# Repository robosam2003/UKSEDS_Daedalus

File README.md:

# UKSEDS Team Daedalus - "In thrust we trust"

The rocket avionics consisted of a Teensy 4.1 for the main microcontoller, a low-g IMU (BNO055), a high-g accelerometer (ADXL377), a pressure sensor (BMP280), a GPS (NEO-6M) and a 433 MHz radio transciever (RFM96W).

The purpose of the rocket was to collect acceleration and gyroscope data such that we could test our IMU based position estimation algorithm (also called dead reckoning).

# Code
The `code` folder contains code for all the sensors and telemetry onboard and for the ground station. The `masterCode` folder contains the final code loaded onto the rocket.

## Sensors and telemetry:
- **BNO055**: Our low-g IMU, containing accelerometers capable of ±16G, as well as very accurate gyroscopes and magnetometers. Big thanks to SunrIde's [Tom Danvers](https://github.com/TomD53) for writing the library we used to interface with the BNO055: [`Arduino-BNO055`](https://github.com/TeamSunride/Arduino-BNO055). 
- **ADXL377**: Our high-g IMU, capable of up to ±200G. This is an analogue sensor and is *very noisy*, so both hardware filters (capacitors) and software filters ([Kalman filters](https://github.com/denyssene/SimpleKalmanFilter)) were used to get accurate data. 
- **BMP280**: A pressure based altimeter used in conjunction with the brilliant [Adafruit library](https://github.com/adafruit/Adafruit_BMP280_Library).
- **NEO-6M**: A cheap but capable GPS module from ublox. In order to get a fast GPS lock, we implemented assisted GPS loading using the ublox AssistNow service. See [`code/NEO6mWithAssistNow`](https://github.com/robosam2003/UKSEDS_Daedalus/tree/main/code/NEO6mWithAssistNow).
- **RFM96W**: A 433MHz SX1272 based tranciever module that was used both onboard and on our ground station. We used the LoRa protocol for greater range. We implemented an interrupt driven method using [`RadioLib`](https://github.com/jgromes/RadioLib).

## Ground station
The ground station used an old arduino nano with the RFM96W to recieve live telemetrics from the rocket. The launch commit button was used to put the rocket into a launch ready state remotely.

It passed this data to Grafana and InfluxDB using the [line protocol](https://docs.influxdata.com/influxdb/cloud/reference/syntax/line-protocol/). Big thanks to SunrIde's [Yomi](https://github.com/abayomi185), [Tom](https://github.com/TomD53) and [Sebastiano](https://github.com/robosam2003/UKSEDS_Daedalus/blob/main/resources/grafanaDashboard.jpg) for building the software to do this [`TeamSunride/GroundStation`](https://github.com/TeamSunride/GroundStation). Our live telemetry Grafana Dashboard is shown below:

### The rocket launch sequence is as follows:
- Ensure ground station is booted and ready.
- **Compile** masterCode/main.cpp and upload to teensy so that the RTC syncs.
- Setup sensors, datalogging and telemety on the ground.
- Full system test with serial output to double check sensor values look reasonable.
- Load avionics into rocket.
- Wait for "Launch commit" from ground station.
- When rocket is loaded on the launch rail, press launch commit button on ground station (wait for confirmation - ground station light should go green).
- Start data acquisition, datalogging and transmitting data.
- Launch!

Loading avionics:

# Circuitry
This rocket used breakout boards to house components. This made testing and verification easier before ordering the final PCB. The PCB was designed in EAGLE using many custom libraries. 

The final schematic:

[`Rocketry_circuit.sch`](https://github.com/robosam2003/UKSEDS_Daedalus/blob/main/circuitry/Rocketry_circuit.sch):

The final pcb board design:

[`Rocketry_circuit.brd`](https://github.com/robosam2003/UKSEDS_Daedalus/blob/main/circuitry/Rocketry_circuit.brd):

The manufactured PCB (from china):   

The assembled pcb with breakouts soldered and mounted:

The avionics recovered after flight:

# Flight data

The launch was a ~success!~... it *went up* anyway. We suspect excess friction on the launch rail caused it to fly off course at about a 45° angle. (See https://www.youtube.com/watch?v=rMJzLpDIJ3U)

The rocket still achieved an apogee of 641m according to the BMP280 altimeter (note that the spike at apogee caused by the pressure from the ejection charge). The GPS lost satellite lock on launch as predicted, but regrained lock after apogee:

The acceleration data followed our expectations from the OpenRocket simulation, with a slightly lower max acceleration of 14.4g. Unfortunately, the BNO055 maxed out at 4G, rather than the desired 16g, despite having configured it to read up to 16g. The ADXL377 data is decent though: (note the spike at ejection charge)

The onboard dead reckoning algorithm also didn't work as expected, due to the BNO055 maxing out earlier than anticipated and due to the initial launch being so oscillatory (which threw off orientation estimation) the data is not an accurate measurement of position. Much has been learned from this launch and will be refined in future rockets. :)

The **telemetry** range was not very good, likely due to bad antennas, and because of UK regulations which limited our transmit power down to 10dbm at a max duty cycle of 10%. :(

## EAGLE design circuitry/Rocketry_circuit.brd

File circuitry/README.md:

This is the folder for circuitry

.brd files contain files relating to pcb placement and copper routing

.sch files contain schematics\n

.pro files contin autorouter data\n

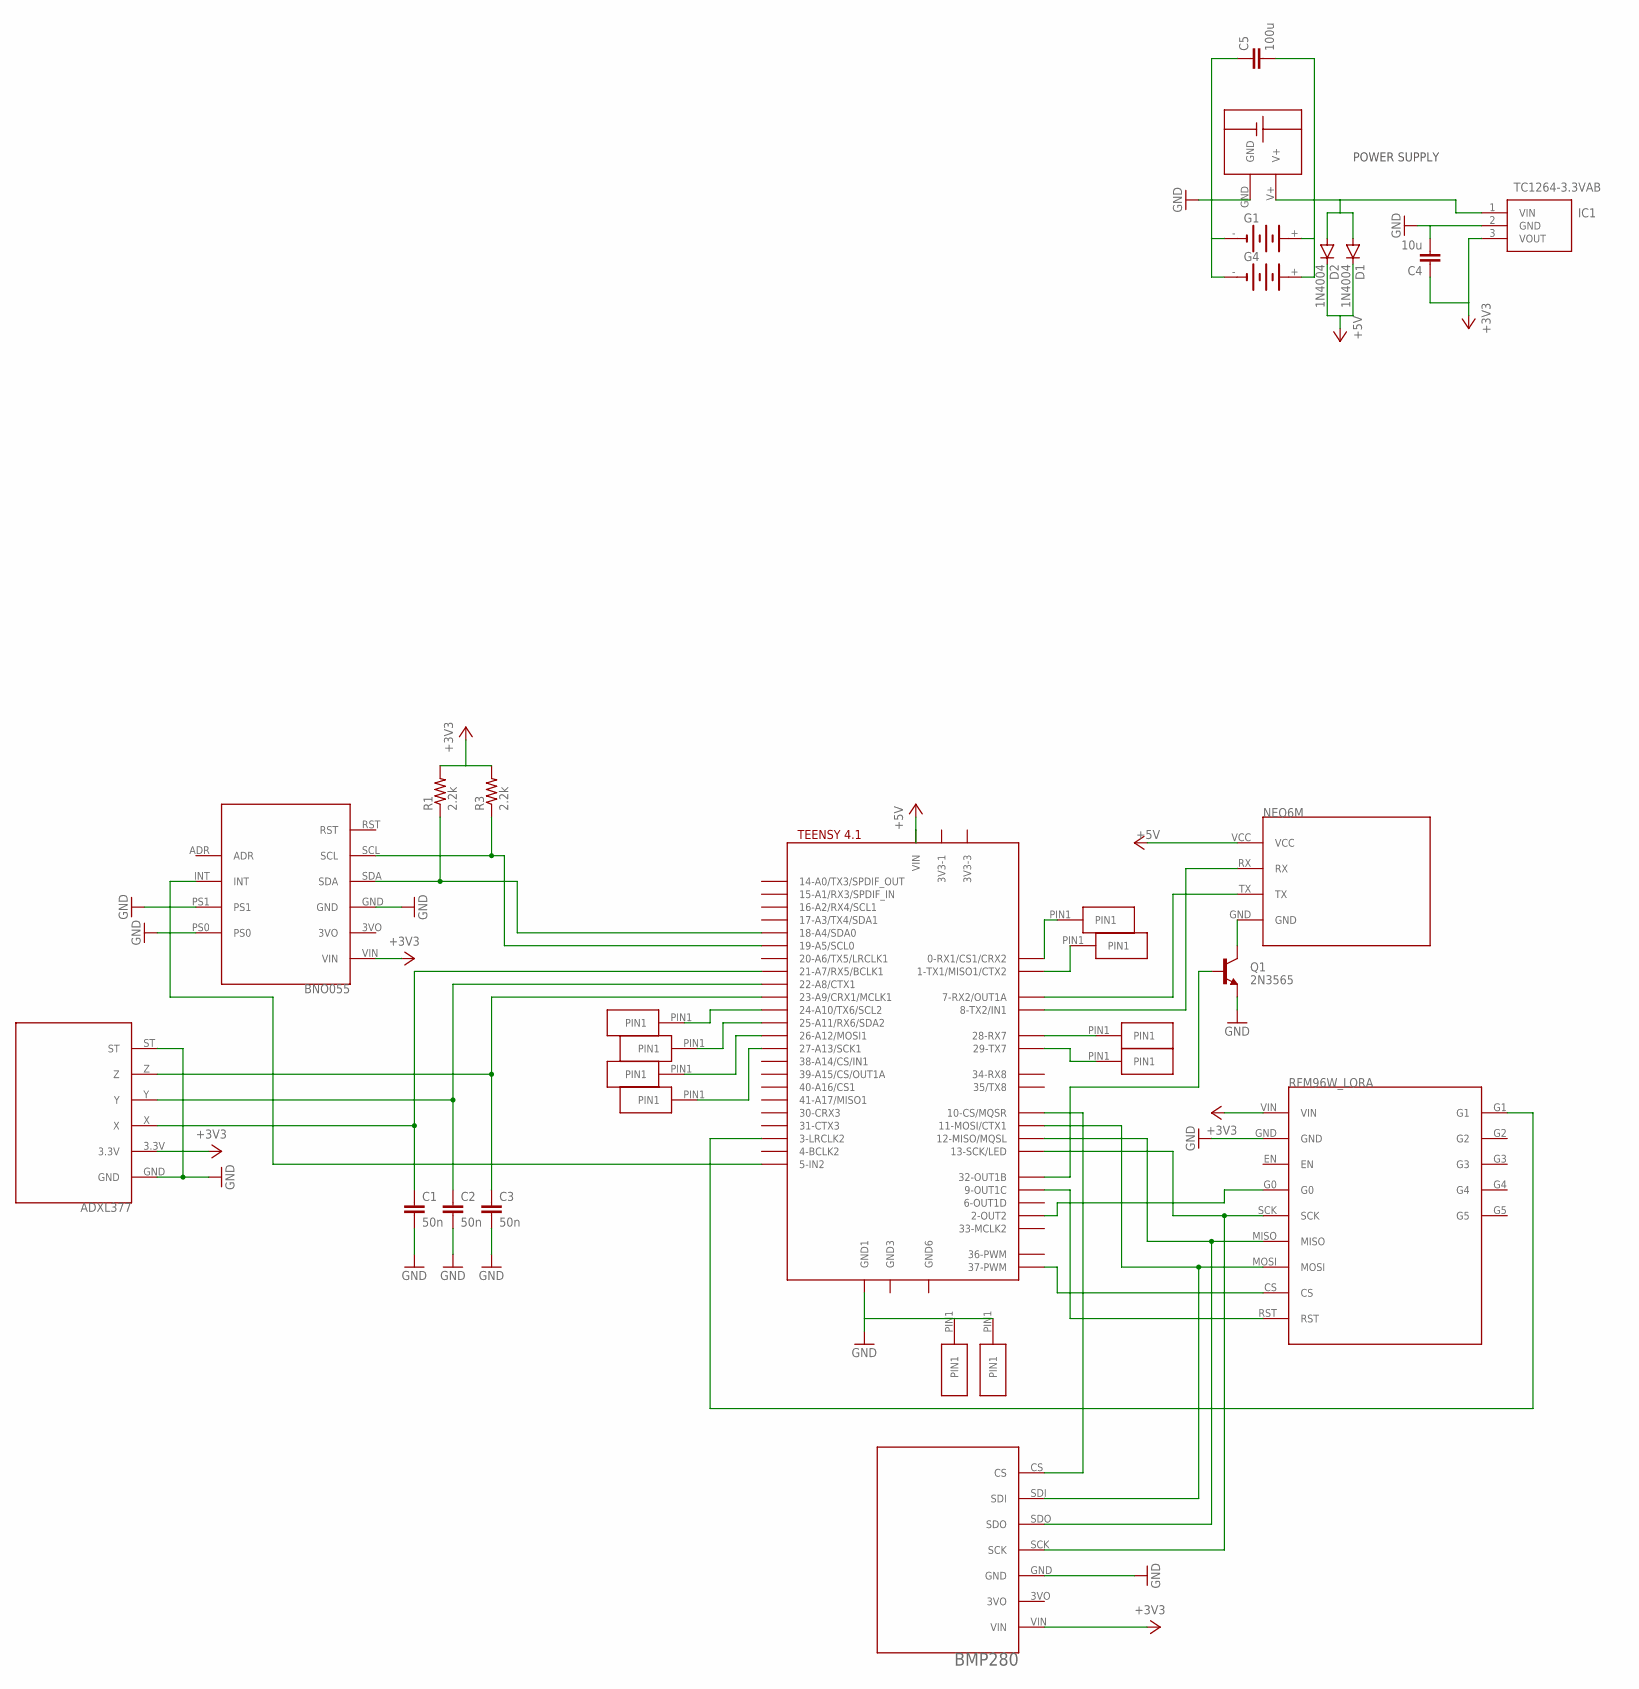
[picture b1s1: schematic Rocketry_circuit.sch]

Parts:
BRKOUT1: BNO055
C1, C2, C3: 50n; C2.5-3
C4: 10u; C2.5-3
C5: 100u; C2.5-3
D1, D2: 1N4004; DO41-10
G1, G4: 3V11R
IC1: TC1264-3.3VAB; TO254P483X988X2222-3P
Q1: 2N3565; TO92
R1, R3: 2.2k; 0207/5V
U$1: TEENSY41
U$2: BMP280
U$3: ADXL377
U$4: NEO6M
U$5: RFM96W
U$6, U$7, U$8, U$9, U$10, U$11, U$13, U$14, U$15, U$16: 1PINOUT
U$12: SMALL_SCREW_TERMINAL

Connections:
+3V3: BRKOUT1.VIN, C4.1, IC1.3 (VOUT), R1.2, R3.2, U$2.VIN, U$3.3.3V, U$5.VIN
+5V: D1.C, D2.C, U$1.VIN, U$4.VCC
GND: BRKOUT1.GND, BRKOUT1.PS0, BRKOUT1.PS1, C1.2, C2.2, C3.2, C4.2, C5.1, G1.-, G4.-, IC1.2 (GND), Q1.3 (E), U$1.GND1, U$2.GND, U$3.GND, U$3.ST, U$5.GND, U$10.PIN1, U$11.PIN1, U$12.GND
unnamed: C1.1, U$1.21-A7/RX5/BCLK1, U$3.X
unnamed: C2.1, U$1.22-A8/CTX1, U$3.Y
unnamed: BRKOUT1.SDA, R1.1, U$1.18-A4/SDA0
unnamed: C3.1, U$1.23-A9/CRX1/MCLK1, U$3.Z
unnamed: BRKOUT1.SCL, R3.1, U$1.19-A5/SCL0
unnamed: U$1.7-RX2/OUT1A, U$4.TX
unnamed: U$1.8-TX2/IN2 (8-TX2/IN1), U$4.RX
unnamed: U$1.13-SCK/LED, U$2.SCK, U$5.SCK
unnamed: U$1.12-MISO/MQSL, U$2.SDO, U$5.MISO
unnamed: U$1.11-MOSI/CTX1, U$2.SDI, U$5.MOSI
unnamed: U$1.37-PWM, U$5.CS
unnamed: C5.2, D1.A, D2.A, G1.+, G4.+, IC1.1 (VIN), U$12.V+
unnamed: BRKOUT1.INT, U$1.5-IN2
unnamed: U$1.2-OUT2, U$5.G0
unnamed: U$1.24-A10/TX6/SCL2, U$9.PIN1
unnamed: U$1.10-CS\MQSR (10-CS/MQSR), U$2.CS
unnamed: U$1.25-A11/RX6/SDA2, U$7.PIN1
unnamed: U$1.28-RX7, U$6.PIN1
unnamed: U$1.3-LRCLK2, U$5.G1
unnamed: U$1.9-OUT1C, U$5.RST
unnamed: U$1.29-TX7, U$8.PIN1
unnamed: U$1.26-A12/MOSI1, U$13.PIN1
unnamed: Q1.2 (B), U$1.32-OUT1B
unnamed: Q1.1 (C), U$4.GND
unnamed: U$1.27-A13/SCK1, U$14.PIN1
unnamed: U$1.0-RX1/CS1/CRX2, U$15.PIN1
unnamed: U$1.1-TX1/MISO1/CTX2, U$16.PIN1

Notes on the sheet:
POWER SUPPLY

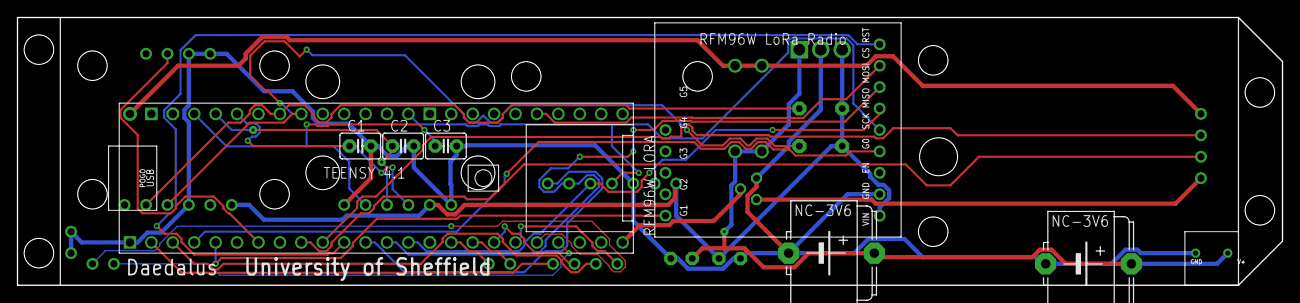
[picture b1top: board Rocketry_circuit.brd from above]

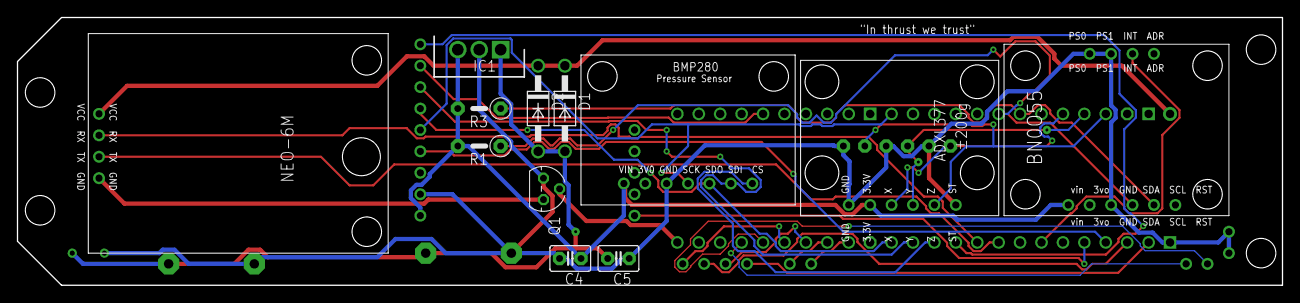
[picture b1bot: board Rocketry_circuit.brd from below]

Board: 2 copper layers, 150.0 x 31.8 mm, 30 parts (12 on the bottom side), 30 nets.

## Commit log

2022-02-15 Commited gitignore
2022-02-15 Made a change on Github.com - Test
2022-02-15 Changed a thing in clion on the playing branch
2022-02-15 made a change in test_branch
2022-02-15 Worked on calibration routine, refining dead reckoning.
2022-02-18 Committed gitignore again
2022-02-18 Added wiring, still to figure out the RF-LORA-915-D data protocol
2022-02-18 edited accuracy
2022-02-21 Wired in the RF-LORA-915-D - Over SPI
2022-02-23 Replaced NEO6M with NEO-M9N and wired it up.
2022-03-02 moved to circuitry folder
2022-03-02 changed name to README.md
2022-03-02 moved to circuitry
2022-03-02 Updated library files (accuracy) and added 3D models. .brd file added
2022-03-02 initial commit from clion
2022-03-02 Added BNO055 code folder
2022-03-02 initial commit from clion 2
2022-03-02 Added BNO055 main src file (copy paste) old version will not be used and old repo will be deleted
2022-03-03 Commit before merging IMU reop
2022-03-03 initial code
2022-03-03 added files manually
2022-03-03 initial commit 2
2022-03-10 Added 3D files and proper footprints for all components, worked on brd design
2022-03-12 Commit before working on calibration routine
2022-03-12 Added rotation matrix function, working on calibration routine. - Currently the absolute value of acceleration is not equal to 9.8
2022-03-12 Accelerometer offsets/biases are now a constant value.
2022-03-14 added a link
2022-03-14 Fixed rotation vector for world to relative coord frame
2022-03-14 Working on calibration routine again, considering setting it constant.
2022-03-15 power circuitry up to date
2022-03-18 updated board size to 31.75mm width, to fit into 34mm transition shoulder section
2022-03-22 Incremental progress - 5V for GPS, interrupt wire, etc
2022-03-26 removed .idea from vs
2022-03-26 made local copy of tom's code, adding some features of my own
2022-03-26 initial commit 3
2022-03-26 performed testing on i2c read speeds - getAllData is buggy - dont use it
2022-03-26 Added removeOffsets() function - constant ACC offsets atm
2022-03-26 Added operator[] to Vector.h - Makes some things a lot easier.
2022-03-26 Updated operator[] - now assignable - no need for setY etc.
2022-03-26 Updated i2c device to check for i2c availability, working on filtering.
2022-03-29 incremental commit
2022-03-29 got FSK working, need to figure out bit rates properly - runnning at full whack means the reciever misses packets.
2022-03-29 Working very well over FSK, bit rate of 300kbps - main issue is that writing to Serial takes a long time, something to consider for our ground station. LoRa might work OK after all - looks like Seria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
2022-03-30 added a transisor and breakouts for spare teensy pins (incase we need them)
2022-03-30 added platformio.ini
2022-03-30 Added ADXL377 code
2022-03-30 Added
2022-03-30 recent
2022-03-30 Added calcRotationVect and findOffsets function - both working well with Vector<double> integration
2022-03-30 added ADXL code, looks like it really needs that capacitor to smooth things over. /:)
2022-03-30 Moved instructions to transmitData(), it seems to be slow though, 5-7ms - needs improvement
2022-03-31 beginning to think LoRa is too slow - testing commit
2022-03-31 LoRa is too slow - 121ms for a packet of any length, using interrupt based method.
2022-03-31 changed entire structure - now writes to the 512 byte buffer before flushing. writing to the buffer takes a few us, but flushing can take up to ~5ms - Investigating ways to make it quicker
2022-03-31 now using SDIO on the sdfat library much quicker if you do it right, now takes only ~1.5ms max per 512 byte buffer write. Looking into preallocating and writing to a single page each time.
2022-03-31 Seems to only achieve fast write speeds when writing quickly - could work for rocket???
2022-04-04 Still trying to achieve faster write speeds, prealloacting makes it 2-3ms faster
2022-04-04 Success! Preallocating memory and writing to a .bin file gets the average write speed down to about 1.5ms for a 512 byte buffer.
2022-04-04 MEGA SUCCESS! - Now using a RingBuffer from the examples provided - getting 177us write time of 512 bytes CONSISTENTLY.
2022-04-04 fixed calcRotationVect functionality - orientaion needs to be anticlockwise->increasing!
2022-04-04 Implemented integration of gyroscopes - still need to do reference frame transfer and investigate higher update rates
2022-04-04 incremental commit - did not change anything
2022-04-04 i2c read time is now at 3.8ms max ????? - very odd behaviour. turns our getAllData was fine all along ??
2022-04-04 implemented first order hold on gyroscope integration
2022-04-04 Implemented first order hold on position and velocity.
2022-04-04 fixed offsets, implemented dead reckoning - Lots of drift - may only be accurate for flight? - work to be done
2022-04-06 LoRa has much better range - working on optimisation - currently aas 64ms between writes.
2022-04-06 - 64ms was for 64 bytes -_- takes 241ms for 255 bytes - I think FSK is out only option.
2022-04-06 Lora is just too slow - Using FSK instead.
2022-04-06 MEGA SUCCESS! - Now only takes ~411us until it is ready to transmit again -_- It works and I don't know why.
2022-04-09 Final sch and brd files - Ordered pcb
2022-04-09 Updated ADXL coded
2022-04-09 Implemented getInitialOrientation() - This is to be called at "launch commit".
2022-04-09 Drift on position is huge - Double integration of acceleration and integration of gyros given massive errors - Considering sensor fusion - Also considering running algo at 400Hz (2.5ms cycle time)
2022-04-12 Experimenting with live accelerometer and gyroscope bias estimation.
2022-04-12 live bias estimation is tricky - not sure why it's not working - needs a proper dry run
2022-04-13 getAllData() works fine now - not an issue.
2022-04-18 added sch, brd, and final production images of pcb
2022-04-27 down to 58ms transmit time at spreading factor of 6, but it doesnt recieve correctly??? - need to do range testing.
2022-04-28 Added final pcb images
2022-04-30 added sendUbx, getUbx, and getUbxFromFile functions, should allow me so see what is happening a bit better.
2022-05-02 upgraded the functions, but it doesnt seem to be working
2022-05-03 Got sendUbx working, config messages now send ACK-ACK, and we are able to see the lat, long, altitude time etc from NAV-POSLLH.
2022-05-03 added teensyRTC code
2022-05-03 added teensyRTC.cpp and teensyRTC.h
2022-05-03 moved code to proper folder, deleted "testmastercode"
2022-05-03 added ADXL377.cpp and ADXL377.h, and added in a updateADXLfilters function
2022-05-03 converted to legacy code - now using toms fancy library
2022-05-03 incremental commit - working on live bias estimation
2022-05-03 added BNO055daedalus.cpp and BNO055daedalus.h
2022-05-03 added SDcardDataLog.cpp and SDcardDataLog.h.
2022-05-03 added RFM96WrecieveFSK.cpp and RFM96WrecieveFSK.h
2022-05-03 added RFM96WtransmitFSK.cpp and RFM96WtransmitFSK.h
2022-05-03 added RFM96WtransmitLORA.cpp and RFM96WtransmitLORA.h
2022-05-03 added RFM96WrecieveLORA.cpp and RFM96WrecieveLORA.h
2022-05-04 added NEO6mWithAssistNow.cpp and NEO6mWithAssistNow.h
2022-05-04 - Added Ash's fancy RTC code - Now re-fixes in 2 seconds. - Fixed getUBX, now the single polling commands work. - Altered GPSweek() and actualTimeOfWeekms() to use ethe getTimeStampMillis() function
2022-05-07 Fixed header files. - must use spreading factor 8 - 175666us (17.6ms) before ready to re-transmit.
2022-05-07 fixed getADXL377 so it now returns a Vector<double>. Added offsets manually.
    NOTES: The sensor seems very noisy when still, but performs well under higher acceleration, which is what we need it for.
2022-05-11 initial commit - added BMP280.cpp and BMP280.h
2022-05-11 tested acquisition time and fixed setup - 175us every time
2022-05-12 Implemented getGPSData() function
2022-05-13 added data structure and writing struct to ringbuf - 31 fields, 248 bytes, Only takes 40us.
2022-05-14 changed timestamp to uint_64 - rb.printf-ing with %llu
2022-05-19 Moved master code to root
2022-05-19 configured master code to use header files from \code folder using lib_extra_dirs
2022-06-02 Using NDOF mode to obtain initial orientation is inaccurate, looking into more complex state estimation techniques (See pdf)
2022-06-02 added ground station RTC sync and updated data logging struct
2022-06-02 Implemented RTC sync in masterCode
2022-06-04 Fixed offset finding and calibration routine for a known flat and stable surface - Now very accurate :)
2022-06-06 Increased gpsSerial BAUD rate, and fixed some config errors. - Note that the 'quick' way to get GPS data is to send the NAV_POSLLH UBX command ~200ms before you actually need it.
2022-06-07 Implemented sending "Launch commit" with the big red button and receiving confirmation message - with LEDs!
2022-06-10 Added parsing of data for Grafana, fixed buggy transmission.
2022-06-10 Now parsing received floats data using unions - much simpler
2022-06-11 Added ADXL377 bias calculation - Surprisingly good with the kalman filter - NOTE: MUST be done after all the other components have been switched on to simulate the same current draw conditions (ADXL3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
2022-06-11 Fixed getInitialOrientation - now gets very accurate orientation when on the launch rail - works best with a bias-compensated sensor.
2022-06-13 Added flight data from the launch (onboard) and a matlab code to graph it
2022-06-13 Added photos
2022-06-13 added flight data graphs
2022-06-13 added launch rail photo
2022-06-13 added loading avionics images
2022-06-13 Added code and flight data section to README
2022-06-14 updated NEO6M README.md
2022-06-14 Added resources folder and updated README
2022-06-14 changed image filename
